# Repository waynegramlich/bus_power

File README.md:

# bus_power

This printed circuit board provides the ability to connect
up to two separate batteries to the bus -- one for powering
logic and the other for powering motors.  The board has
polarity protection circuitry to deal with accidentally
connecting the power up backwards.  In addition there are
polyfuses (which are kind of like circuit breakers) that protect
against accidental shorts.

## MOSFET Polarity Protection Video

There is a nifty
[YouTube video](https://www.youtube.com/watch?v=IrB-FPcv1Dc)
that explains how a P-channel MOSFET polarity protection circuit
works.

## Revision A

The revision A schematic can be found in the `rev_a` directory
in either `bus_power.pdf` or `bus_power.svg`.  Some relevant
data sheets can be found in the `docs` folder.

The motor (i.e. battery) power can be connected to either N4 or N5
which can be used daisy chain to other power connecors.  N3 is
an Emergency Stop connector.  If you do not have an emergency
stop button this connector must have a wire that shorts between
pins 1 and 2.  The positive power is run through a P-channel
MOSFET (Q1) for polarity protection.  A MOSFET has a much lower
voltage loss than silicon diodes or Schottky diodes.  The power
then goes through a 3 Ampere polyfuse (R2).  If 3 Amperes
is exceeded, the polyfuse will warm up and go into a high resistance
state.  Finally, the power goes through SW1, which is a double
pole, single through switch to the bus connector N2.

The logic power goes through two daisy chain connectors (N6, N7),
a P-channel polarity protection MOSFET (Q2), a 3 Ampere polyfuse
(R3) and the switch (SW1) before providing logic power to the
bus connector (N2).

If this board is at the end of the bus, the termination jumper
(J1) can be connected between pins 1 and 2 to provide 120 Ohms
of bus termination via R1.

## Revision A Issues

* Power switch does not control daisy chain power.

* The bus connector should be centered.

* Provide a power on/off LED.

## Revision B Issues

* There is request for a jumperable power LED.

* Are terminal blocks oriented backwards?

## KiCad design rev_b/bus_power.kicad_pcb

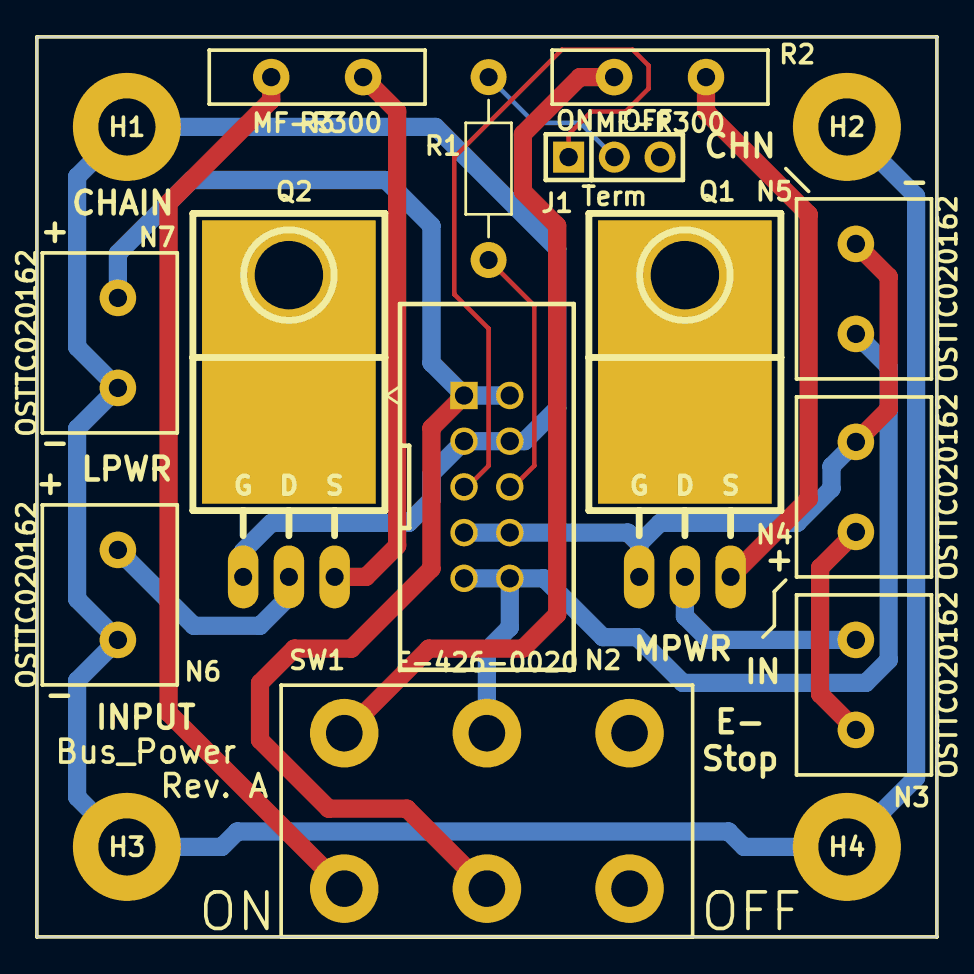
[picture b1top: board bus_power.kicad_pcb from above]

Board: 2 copper layers, 50.0 x 50.0 mm, 18 parts (1 on the bottom side), 14 nets.

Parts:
G1: OSHW_LOGO; OSHW_LOGO_400mil
H1, H2, H3, H4: 3MM_HOLE; MountingHole_3mm
J1: TERMINATE_JUMPER; Pin_Header_Straight_1x03
N2: BUS_MASTER_HEADER; Pin_Header_Straight_2x05_Shrouded
N3, N4, N5, N6, N7: OSTTC020162; 5MM_TERMINAL_BLOCK_2_POS
Q1, Q2: FQP47P06; TO-220_FET-GDS_Horizontal_LargePads
R1: 120 1%; Resistor_Horizontal_400
R2, R3: MF-R300; MF_R300
SW1: F-426-0020; GF_426_0020

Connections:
/LGND: H1.1, H2.1, H3.1, H4.1, N2.3, N2.4, N6.1, N7.1, Q2.G
/LPWR1: N6.2, Q2.D
/LPWR2: Q2.S, R3.1
/LPWR3: R3.2, SW1.4
/LPWR4: N2.1, N2.2, N7.2, SW1.5
/MGND: N2.7, N2.8, N4.1, N5.1, Q1.G
/MPWR0: N3.2, N4.2
/MPWR1: N3.1, Q1.D
/MPWR2: Q1.S, R2.1
/MPWR3: R2.2, SW1.1
/MPWR4: N2.9, N2.10, N5.2, SW1.2
unnamed: J1.1, N2.5
unnamed: J1.2, R1.1
unnamed: N2.6, R1.2

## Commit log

2014-08-11 Initial clone of mini_power.
2014-08-11 Finnished Revision A layout.
2014-08-18 Added silkscreen outline.
2014-10-02 Made a local fp-lib-table.
2014-10-02 A little more work with the library tables.
2014-10-02 Cloned Rev. B. from Rev. A
2014-10-02 Did first layout of Rev. B.
2014-10-02 Forgot to update schematic.
2014-10-30 Wrapped up Rev. B
